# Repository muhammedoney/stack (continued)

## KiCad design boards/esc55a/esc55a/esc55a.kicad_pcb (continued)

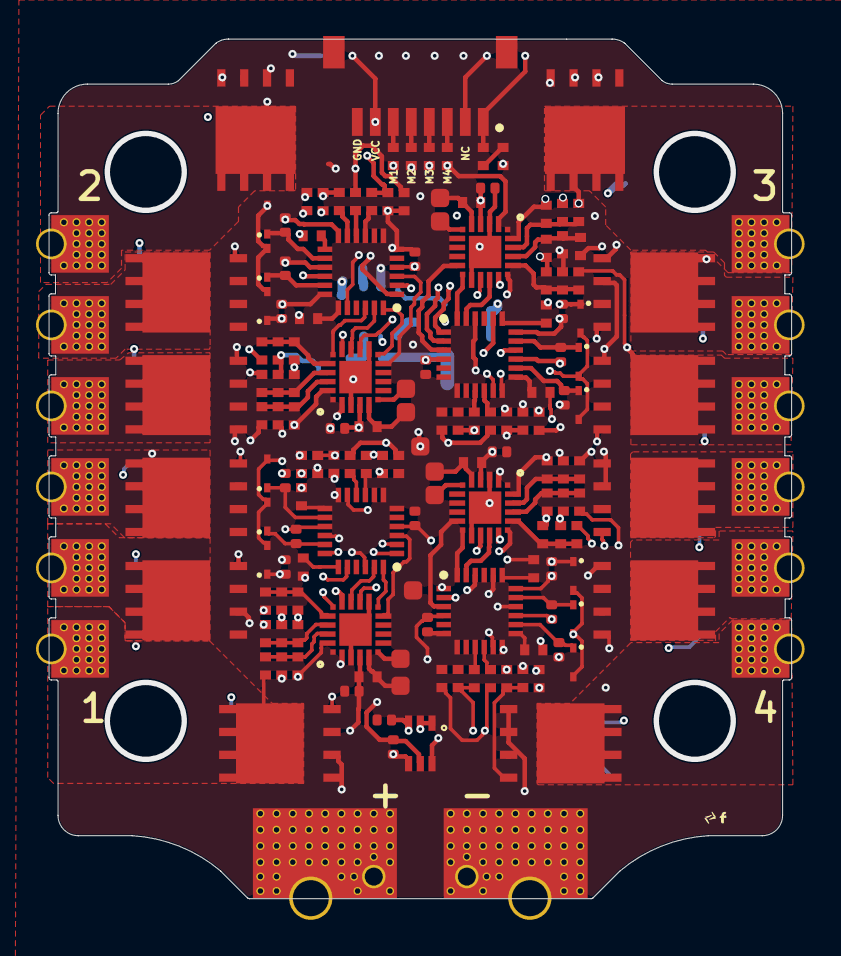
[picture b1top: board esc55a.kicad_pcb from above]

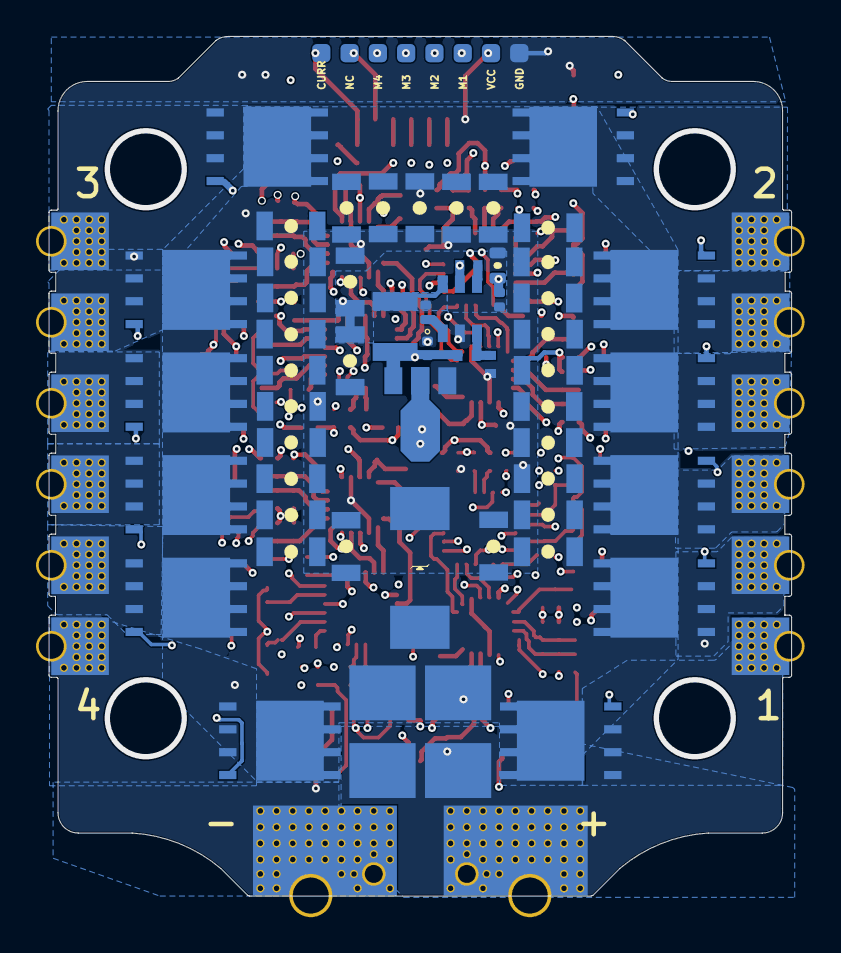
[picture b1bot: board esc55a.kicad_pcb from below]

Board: 4 copper layers, 41.3 x 47.8 mm, 224 parts (62 on the bottom side), 141 nets.
